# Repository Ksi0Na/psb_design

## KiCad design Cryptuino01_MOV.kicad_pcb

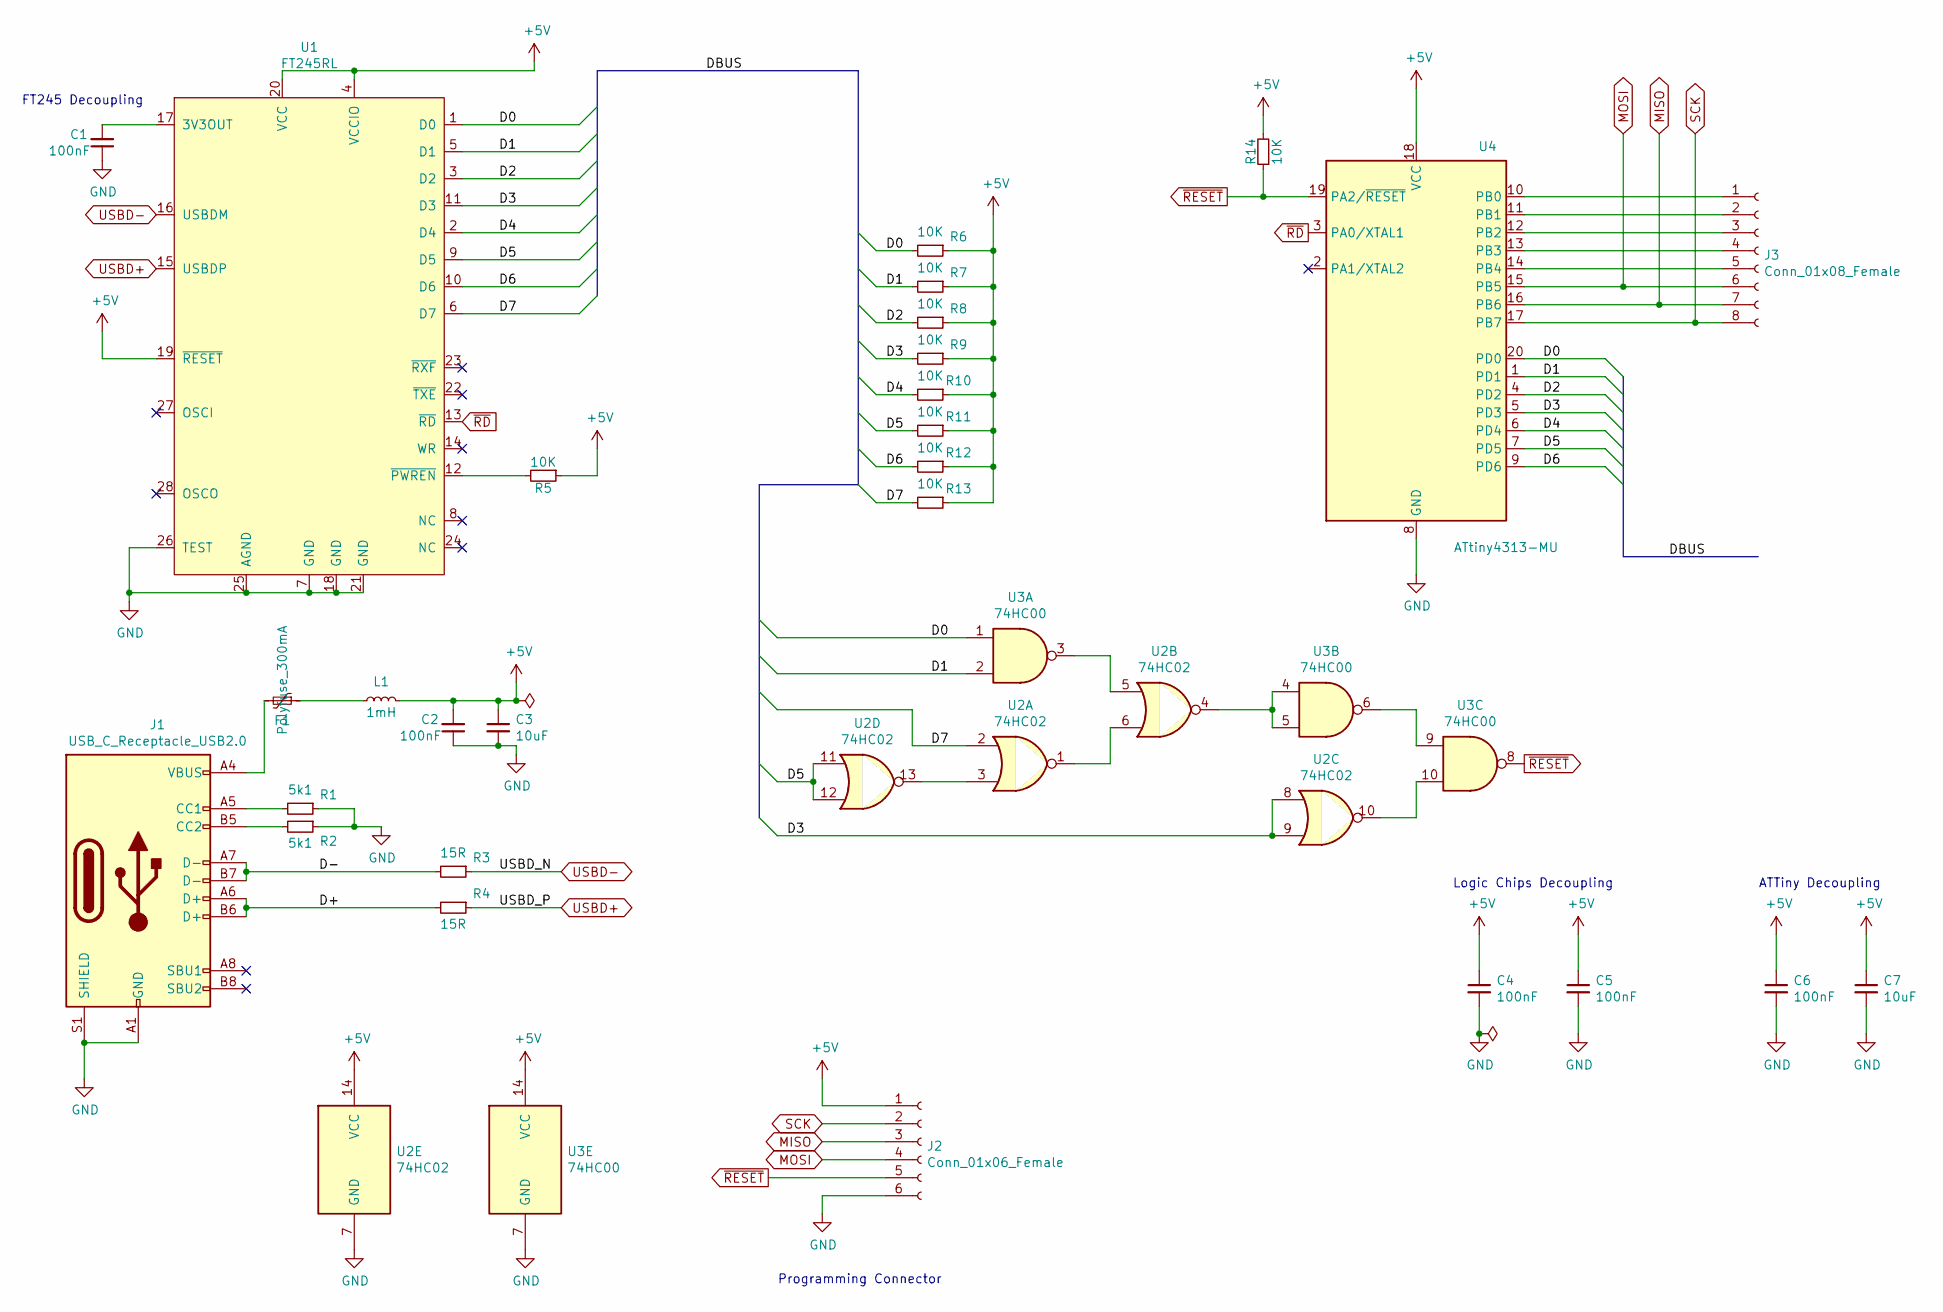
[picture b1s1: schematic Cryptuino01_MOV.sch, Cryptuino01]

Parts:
C1, C2, C4, C5, C6: 100nF; R_0805_2012Metric
C3, C7: 10uF; R_0805_2012Metric
F1: Polyfuse_300mA; R_0805_2012Metric
J1: USB_C_Receptacle_USB2.0; USB_C_Receptacle_HRO_TYPE-C-31-M-12
J2: Conn_01x06_Female; PinSocket_1x06_P2.54mm_Vertical
J3: Conn_01x08_Female; PinSocket_1x08_P2.54mm_Vertical
L1: 1mH; R_0805_2012Metric
R1, R2: 5k1; R_0805_2012Metric
R3, R4: 15R; R_0805_2012Metric
R5, R6, R7, R8, R9, R10, R11, R12, R13, R14: 10K; R_0805_2012Metric
U1: FT245RL; SSOP-28_5.3x10.2mm_P0.65mm
U2: 74HC02; SOIC-14_3.9x8.7mm_P1.27mm
U3: 74HC00; SOIC-14_3.9x8.7mm_P1.27mm
U4: ATtiny4313-MU; QFN-20-1EP_5x5mm_P0.65mm_EP3.35x3.35mm

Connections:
+5V: C2.2, C3.1, C4.1, C5.1, C6.1, C7.1, J2.1, L1.2, R5.1, R6.1, R7.1, R8.1, R9.1, R10.1, R11.1, R12.1, R13.1, R14.2, U1.4 (VCCIO), U1.19 (~RESET), U1.20 (VCC), U2.14 (VCC), U3.14 (VCC), U4.18 (VCC)
/D0: R6.2, U1.1 (D0), U3.1, U4.20 (PD0)
/D1: R7.2, U1.5 (D1), U3.2, U4.1 (PD1)
/D2: R8.2, U1.3 (D2), U4.4 (PD2)
/D3: R9.2, U1.11 (D3), U2.8, U2.9, U4.5 (PD3)
/D4: R10.2, U1.2 (D4), U4.6 (PD4)
/D5: R11.2, U1.9 (D5), U2.11, U2.12, U4.7 (PD5)
/D6: R12.2, U1.10 (D6), U4.9 (PD6)
/D7: R13.2, U1.6 (D7), U2.2
/D+: J1.A6 (D+), J1.B6 (D+), R4.2
/D-: J1.A7 (D-), J1.B7 (D-), R3.2
GND: C1.1, C2.1, C3.2, C4.2, C5.2, C6.2, C7.2, J1.A1 (GND), J1.A12 (GND), J1.B1 (GND), J1.B12 (GND), J1.S1 (SHIELD), J2.6, R1.1, R2.1, U1.7 (GND), U1.18 (GND), U1.21 (GND), U1.25 (AGND), U1.26 (TEST), U2.7 (GND), U3.7 (GND), U4.8 (GND), U4.21 (GND)
MISO: J2.3, J3.7, U4.16 (PB6)
MOSI: J2.4, J3.6, U4.15 (PB5)
unnamed: C1.2, U1.17 (3V3OUT)
unnamed: F1.1, L1.1
unnamed: F1.2, J1.A4 (VBUS), J1.A9 (VBUS), J1.B4 (VBUS), J1.B9 (VBUS)
unnamed: J1.A5 (CC1), R1.2
unnamed: J1.B5 (CC2), R2.2
unnamed: J3.1, U4.10 (PB0)
unnamed: J3.2, U4.11 (PB1)
unnamed: J3.3, U4.12 (PB2)
unnamed: J3.4, U4.13 (PB3)
unnamed: J3.5, U4.14 (PB4)
unnamed: R5.2, U1.12 (~PWREN)
unnamed: U2.1, U2.6
unnamed: U2.4, U3.4, U3.5
unnamed: U2.5, U3.3
unnamed: U2.10, U3.10
unnamed: U2.3, U2.13
unnamed: U3.6, U3.9
SCK: J2.2, J3.8, U4.17 (PB7)
USBD+: R4.1, U1.15 (USBDP)
USBD-: R3.1, U1.16 (USBDM)
~RD: U1.13 (~RD), U4.3 (PA0/XTAL1)
~RESET: J2.5, R14.1, U3.8, U4.19 (PA2/~RESET)

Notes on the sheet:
ATTiny Decoupling
Logic Chips Decoupling
Programming Connector
FT245 Decoupling

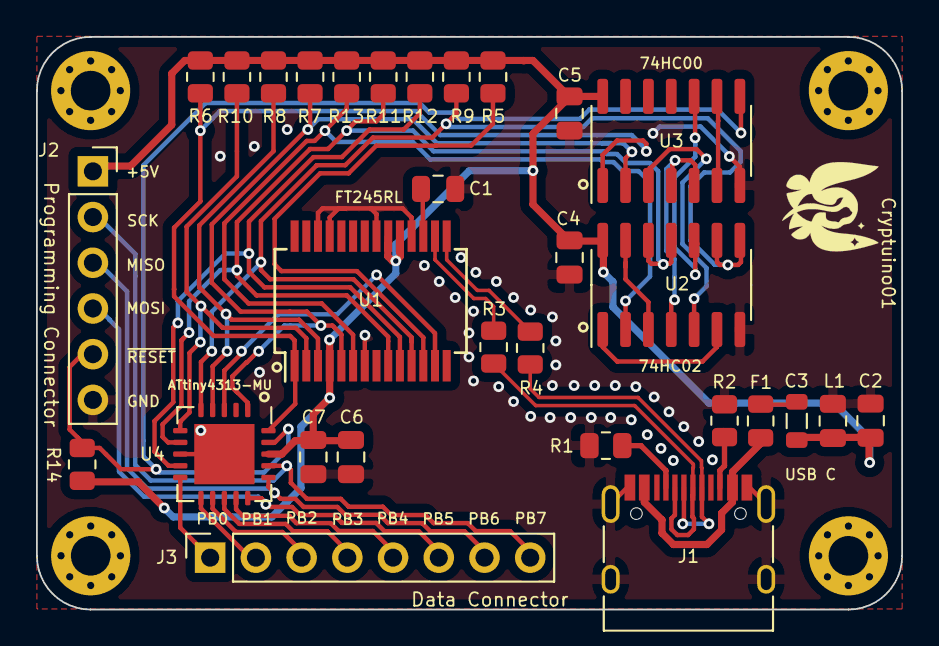
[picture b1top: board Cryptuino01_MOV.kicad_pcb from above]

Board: 2 copper layers, 48.1 x 31.8 mm, 30 parts (0 on the bottom side), 36 nets.

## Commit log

2021-01-03 Cryptuino01_MOV
2021-01-14 done_nice_now
